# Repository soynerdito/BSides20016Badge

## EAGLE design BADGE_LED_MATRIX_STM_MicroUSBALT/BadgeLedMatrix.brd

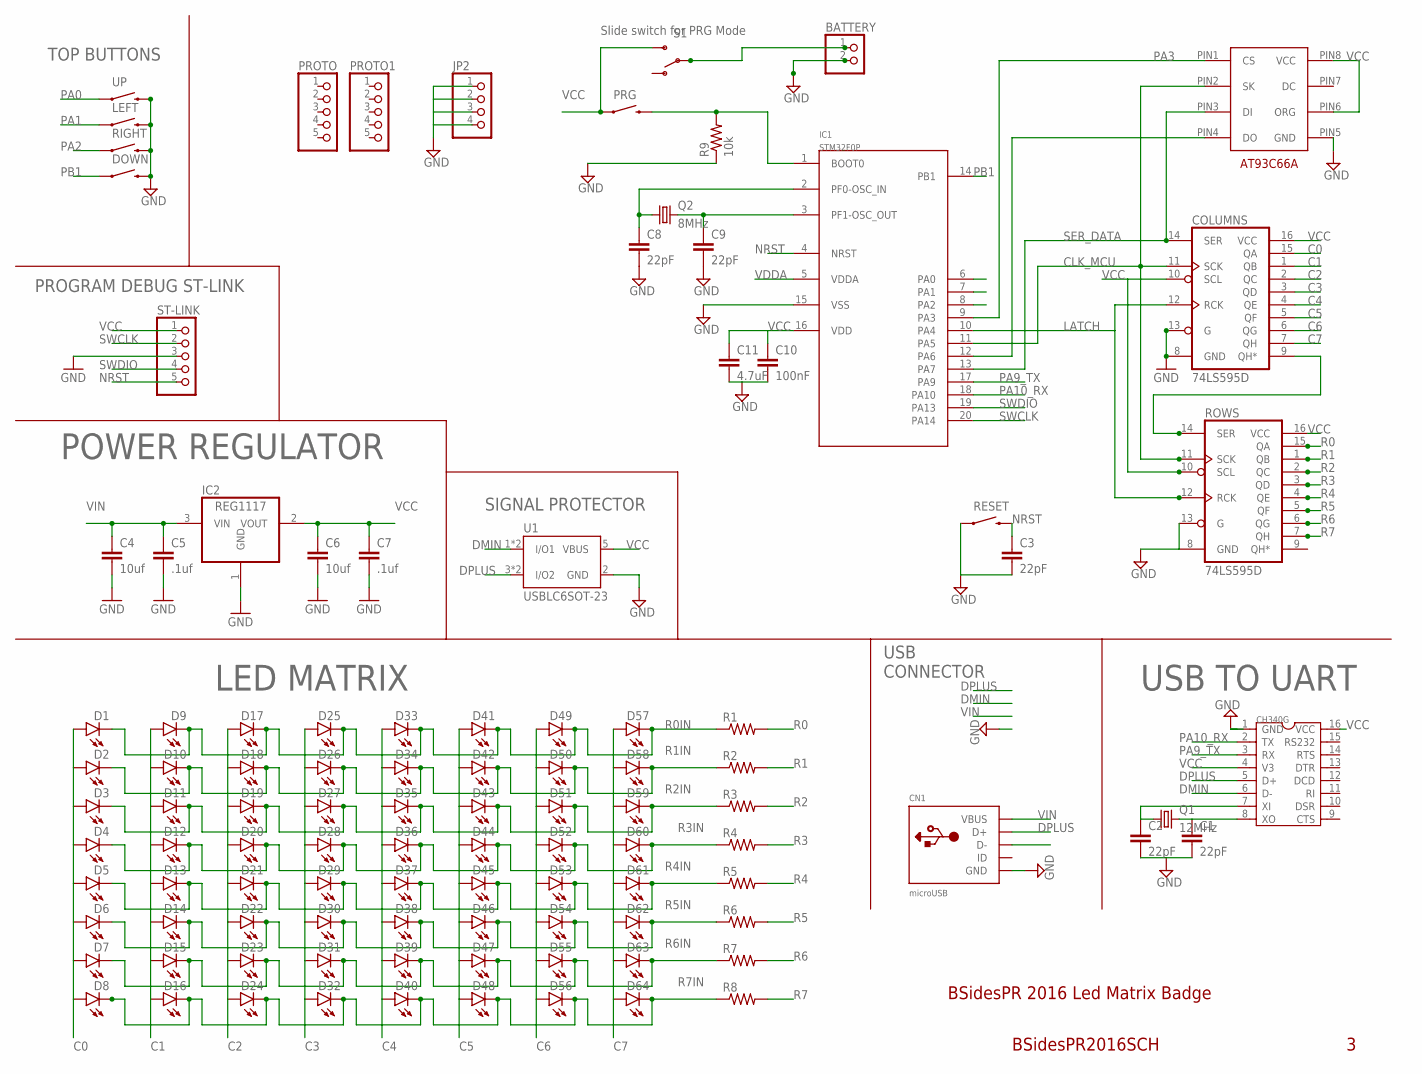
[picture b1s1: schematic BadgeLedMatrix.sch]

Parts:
BATTERY: PINHD-1X2; 1X02
C1, C2, C3, C8, C9: 22pF; 0603-CAP
C4, C6: 10uf; 0603-CAP
C5, C7: .1uf; 0603-CAP
C10: 100nF; 0603-CAP
C11: 4.7uF; 0603-CAP
CH340G: CH340GCH340G; SOP-16
CN1: microUSB; 4UCONN_20329
COLUMNS: 74LS595D; SO16
D1, D2, D3, D4, D5, D6, D7, D8, D9, D10, D11, D12, D13, D14, D15, D16, D17, D18, D19, D20, D21, D22, D23, D24, D25, D26, D27, D28, D29, D30, D31, D32, D33, D34, D35, D36, D37, D38, D39, D40, D41, D42, D43, D44, D45, D46, D47, D48, D49, D50, D51, D52, D53, D54, D55, D56, D57, D58, D59, D60, D61, D62, D63, D64: LED0603; LED-0603
DOWN: SWITCH-MOMENTARY-2SMD-REDUNDANT; TACTILE-SWITCH-SMD
IC1: STM32F0P; TSSOP20
IC2: REG1117; SOT223
JP2: PINHD-1X4; 1X04
LEFT: SWITCH-MOMENTARY-2SMD-REDUNDANT; TACTILE-SWITCH-SMD
PRG: SWITCH-MOMENTARY-2SMD-REDUNDANT; TACTILE-SWITCH-SMD
PROTO, PROTO1: PINHD-1X5; 1X05
Q1: 12MHz; HC49U70
Q2: 8MHz; HC49U70
R1, R2, R3, R4, R5, R6, R7, R8: RESISTOR0603-RES; 0603-RES
R9: 10k; 0603-RES
RESET: SWITCH-MOMENTARY-2SMD-REDUNDANT; TACTILE-SWITCH-SMD
RIGHT: SWITCH-MOMENTARY-2SMD-REDUNDANT; TACTILE-SWITCH-SMD
ROWS: 74LS595D; SO16
S1: SWITCH-SPDT-SMD-A; SWITCH-SPST-SMD-A
ST-LINK: PINHD-1X5; 1X05
U1: USBLC6SOT-23; SOT23-6
U$6: AT93C66A; SOP-8
UP: SWITCH-MOMENTARY-2SMD-REDUNDANT; TACTILE-SWITCH-SMD

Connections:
C0: COLUMNS.15 (QA), D1.A, D2.A, D3.A, D4.A, D5.A, D6.A, D7.A, D8.A
C1: COLUMNS.1 (QB), D9.A, D10.A, D11.A, D12.A, D13.A, D14.A, D15.A, D16.A
C2: COLUMNS.2 (QC), D17.A, D18.A, D19.A, D20.A, D21.A, D22.A, D23.A, D24.A
C3: COLUMNS.3 (QD), D25.A, D26.A, D27.A, D28.A, D29.A, D30.A, D31.A, D32.A
C4: COLUMNS.4 (QE), D33.A, D34.A, D35.A, D36.A, D37.A, D38.A, D39.A, D40.A
C5: COLUMNS.5 (QF), D41.A, D42.A, D43.A, D44.A, D45.A, D46.A, D47.A, D48.A
C6: COLUMNS.6 (QG), D49.A, D50.A, D51.A, D52.A, D53.A, D54.A, D55.A, D56.A
C7: COLUMNS.7 (QH), D57.A, D58.A, D59.A, D60.A, D61.A, D62.A, D63.A, D64.A
CLK_MCU: COLUMNS.11 (SCK), IC1.11 (PA5), ROWS.11 (SCK), U$6.PIN2 (SK)
DMIN: CH340G.6 (D-), CN1.D-, U1.1 (I/O1), U1.4 (I/O1)
DPLUS: CH340G.5 (D+), CN1.D+, U1.3 (I/O2), U1.6 (I/O2)
GND: BATTERY.2, C1.2, C2.2, C3.2, C4.2, C5.2, C6.2, C7.2, C8.2, C9.2, C10.2, C11.2, CH340G.1 (GND), CN1.BASE@1 (GND), CN1.BASE@2 (GND), CN1.GND, CN1.SPRT@1 (GND), CN1.SPRT@2 (GND), CN1.SPRT@3 (GND), CN1.SPRT@4 (GND), COLUMNS.8 (GND), COLUMNS.13 (G), DOWN.3 (2), DOWN.4 (2), IC1.15 (VSS), IC2.1 (GND), JP2.1, JP2.2, JP2.3, JP2.4, LEFT.3 (2), LEFT.4 (2), R9.1, RESET.1, RESET.2 (1), RIGHT.3 (2), RIGHT.4 (2), ROWS.8 (GND), ROWS.13 (G), ST-LINK.3, U1.2 (GND), U$6.PIN5 (GND), UP.3 (2), UP.4 (2)
LATCH: COLUMNS.12 (RCK), IC1.10 (PA4), ROWS.12 (RCK)
unnamed: C9.1, IC1.3 (PF1-OSC_OUT), Q2.2
unnamed: C8.1, IC1.2 (PF0-OSC_IN), Q2.1
unnamed: IC1.1 (BOOT0), PRG.3 (2), PRG.4 (2), R9.2
unnamed: BATTERY.1, S1.2
NRST: C3.1, IC1.4 (NRST), RESET.3 (2), RESET.4 (2), ST-LINK.5
OVERFLOW: COLUMNS.9 (QH*), ROWS.14 (SER)
PA0: IC1.6 (PA0), UP.1, UP.2 (1)
PA1: IC1.7 (PA1), LEFT.1, LEFT.2 (1)
PA2: IC1.8 (PA2), RIGHT.1, RIGHT.2 (1)
PA3: IC1.9 (PA3), U$6.PIN1 (CS)
PA6: IC1.12 (PA6), U$6.PIN4 (DO)
PA9_TX: CH340G.3 (RX), IC1.17 (PA9)
PA10_RX: CH340G.2 (TX), IC1.18 (PA10)
PB1: DOWN.1, DOWN.2 (1), IC1.14 (PB1)
R0: R1.2, ROWS.15 (QA)
R0IN: D1.C, D9.C, D17.C, D25.C, D33.C, D41.C, D49.C, D57.C, R1.1
R1: R2.2, ROWS.1 (QB)
R1IN: D2.C, D10.C, D18.C, D26.C, D34.C, D42.C, D50.C, D58.C, R2.1
R2: R3.2, ROWS.2 (QC)
R2IN: D3.C, D11.C, D19.C, D27.C, D35.C, D43.C, D51.C, D59.C, R3.1
R3: R4.2, ROWS.3 (QD)
R3IN: D4.C, D12.C, D20.C, D28.C, D36.C, D44.C, D52.C, D60.C, R4.1
R4: R5.2, ROWS.4 (QE)
R4IN: D5.C, D13.C, D21.C, D29.C, D37.C, D45.C, D53.C, D61.C, R5.1
R5: R6.2, ROWS.5 (QF)
R5IN: D6.C, D14.C, D22.C, D30.C, D38.C, D46.C, D54.C, D62.C, R6.1
R6: R7.2, ROWS.6 (QG)
R6IN: D7.C, D15.C, D23.C, D31.C, D39.C, D47.C, D55.C, D63.C, R7.1
R7: R8.2, ROWS.7 (QH)
R7IN: D8.C, D16.C, D24.C, D32.C, D40.C, D48.C, D56.C, D64.C, R8.1
SER_DATA: COLUMNS.14 (SER), IC1.13 (PA7), U$6.PIN3 (DI)
SWCLK: IC1.20 (PA14), ST-LINK.2
SWDIO: IC1.19 (PA13), ST-LINK.4
VCC: C6.1, C7.1, C10.1, C11.1, CH340G.4 (V3), CH340G.16 (VCC), COLUMNS.10 (SCL), COLUMNS.16 (VCC), IC1.16 (VDD), IC2.2 (VOUT), PRG.1, PRG.2 (1), ROWS.10 (SCL), ROWS.16 (VCC), S1.3 (S), ST-LINK.1, U1.5 (VBUS), U$6.PIN6 (ORG), U$6.PIN8 (VCC)
VDDA: IC1.5 (VDDA)
VIN: C4.1, C5.1, CN1.VBUS, IC2.3 (VIN)
XI: C2.1, CH340G.7 (XI), Q1.1
XO: C1.1, CH340G.8 (XO), Q1.2

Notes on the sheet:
POWER REGULATOR
LED MATRIX
USB TO UART
USB CONNECTOR
SIGNAL PROTECTOR
BSidesPR 2016 Led Matrix Badge
BSidesPR2016SCH
PROGRAM DEBUG ST-LINK
TOP BUTTONS
Slide switch for PRG Mode

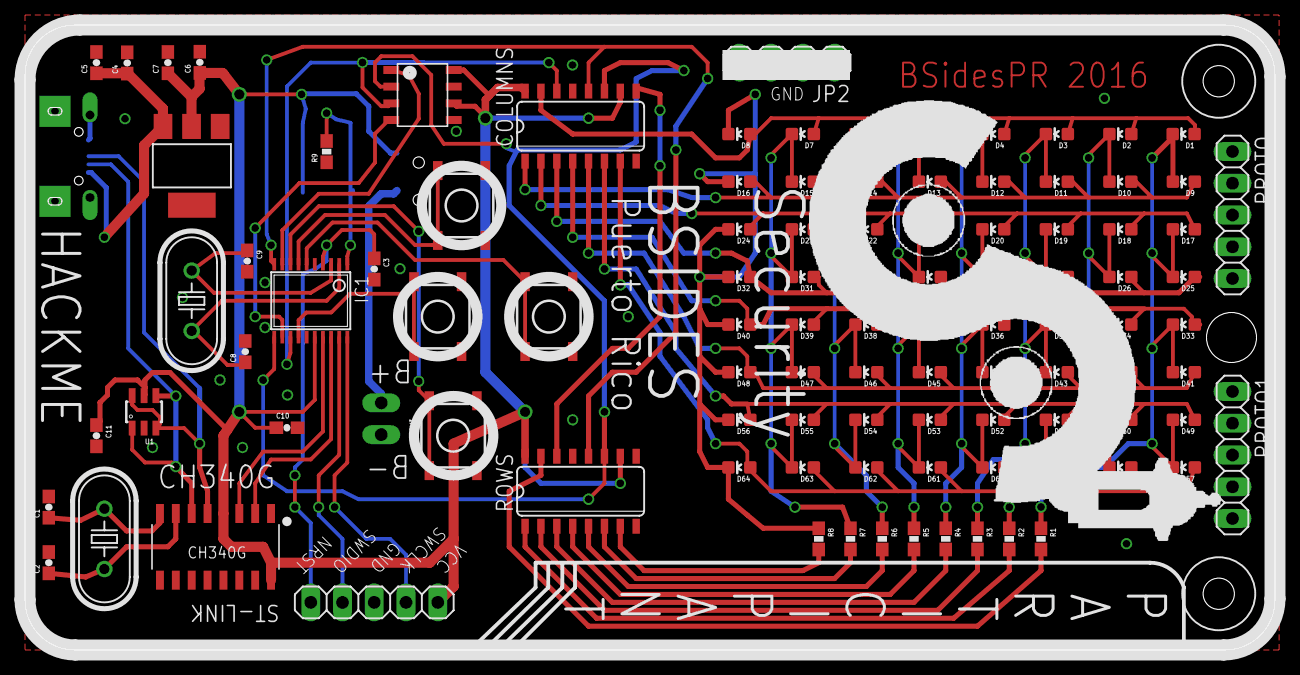
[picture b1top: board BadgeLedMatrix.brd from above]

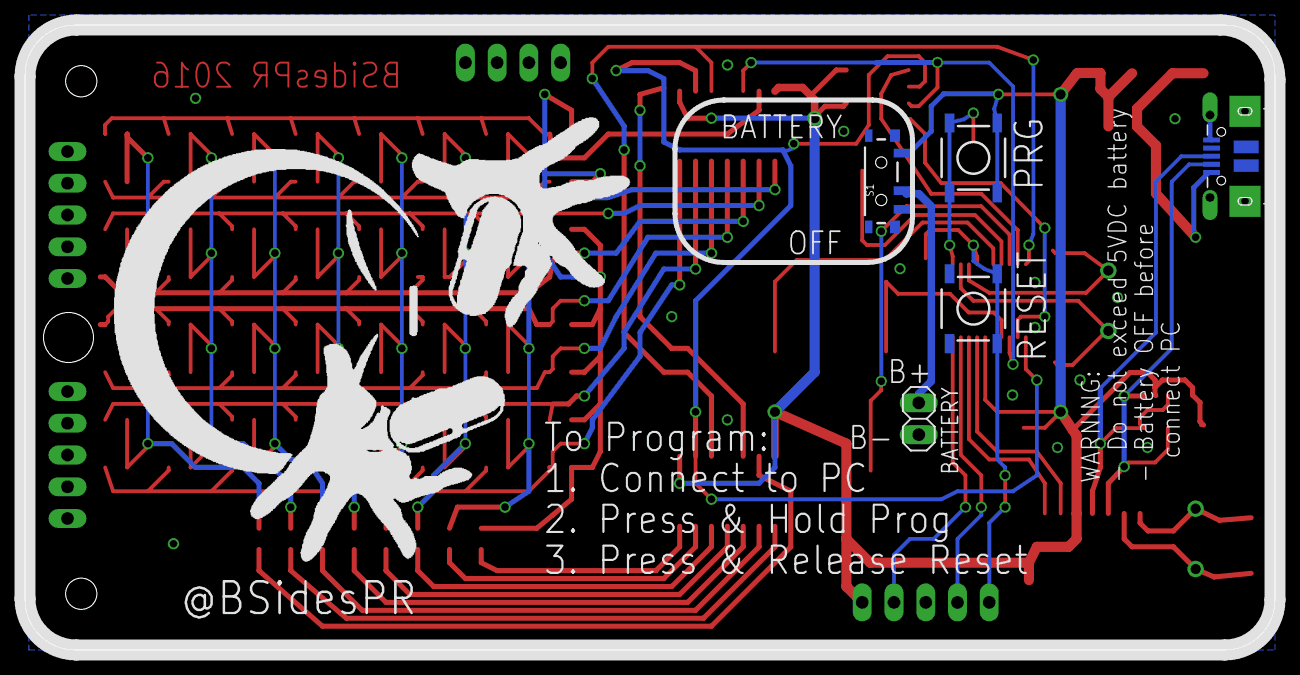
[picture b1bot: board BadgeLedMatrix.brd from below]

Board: 2 copper layers, 100.0 x 50.0 mm, 110 parts (5 on the bottom side), 50 nets.

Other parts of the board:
U$1: OBSIDISLOGO_BOTTOM
U$2: BSIDES_LOGO_NTB_PIC_ONLY
U$3, U$5: DRIL-2,5

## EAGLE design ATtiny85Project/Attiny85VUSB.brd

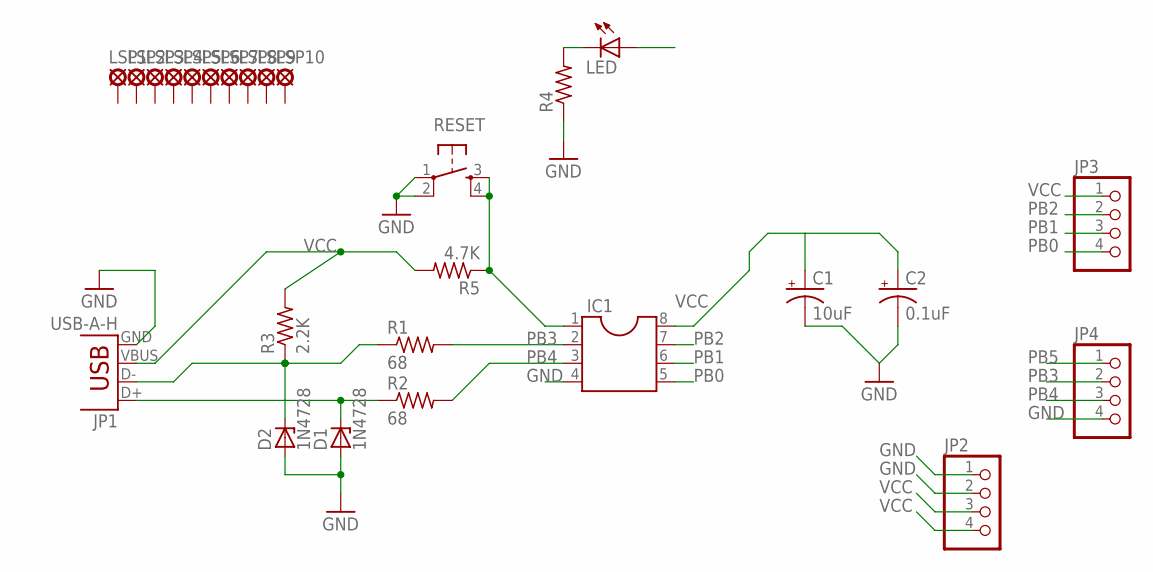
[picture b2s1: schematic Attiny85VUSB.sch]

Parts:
C1: 10uF; CPOL-RADIAL-100UF-25V
C2: 0.1uF; CPOL-RADIAL-100UF-25V
D1, D2: 1N4728; DO41Z10
IC1: ATTINY85TESTS; SOCKET-08
JP1: USB-A-H
JP2, JP3, JP4: PINHD-1X4; 1X04
LED: LED5MM
LSP1, LSP2, LSP3, LSP4, LSP5, LSP6, LSP7, LSP8, LSP9, LSP10: MCS08
R1, R2: 68; 0207/9
R3: 2.2K; 0207/9
R4: R-US_0207/9; 0207/9
R5: 4.7K; 0207/9
RESET: TAC_SWITCHPTH; TACTILE-PTH

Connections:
DMIN: D2.C, JP1.D-, R1.1, R3.1
DPLUS: D1.C, JP1.D+, R2.1
GND: C1.2 (-), C2.2 (-), D1.A, D2.A, IC1.4 (GND), JP1.GND, JP2.1, JP2.2, JP4.4, R4.1, RESET.1, RESET.2
unnamed: LED.K (C), R4.2
PB0: IC1.5 (PB0MOSI), JP3.4
PB1: IC1.6 (PB1_MISO), JP3.3, LED.A
PB2: IC1.7 (PB2SCK), JP3.2
PB3: IC1.2 (PB3_CLKI), JP4.2, R1.2
PB4: IC1.3 (PB4_CLKO), JP4.3, R2.2
PB5: JP4.1
RESET: IC1.1 (PB5_~RESET), R5.1, RESET.3, RESET.4
VCC: C1.1 (+), C2.1 (+), IC1.8 (VCC), JP1.VBUS, JP2.3, JP2.4, JP3.1, R3.2, R5.2

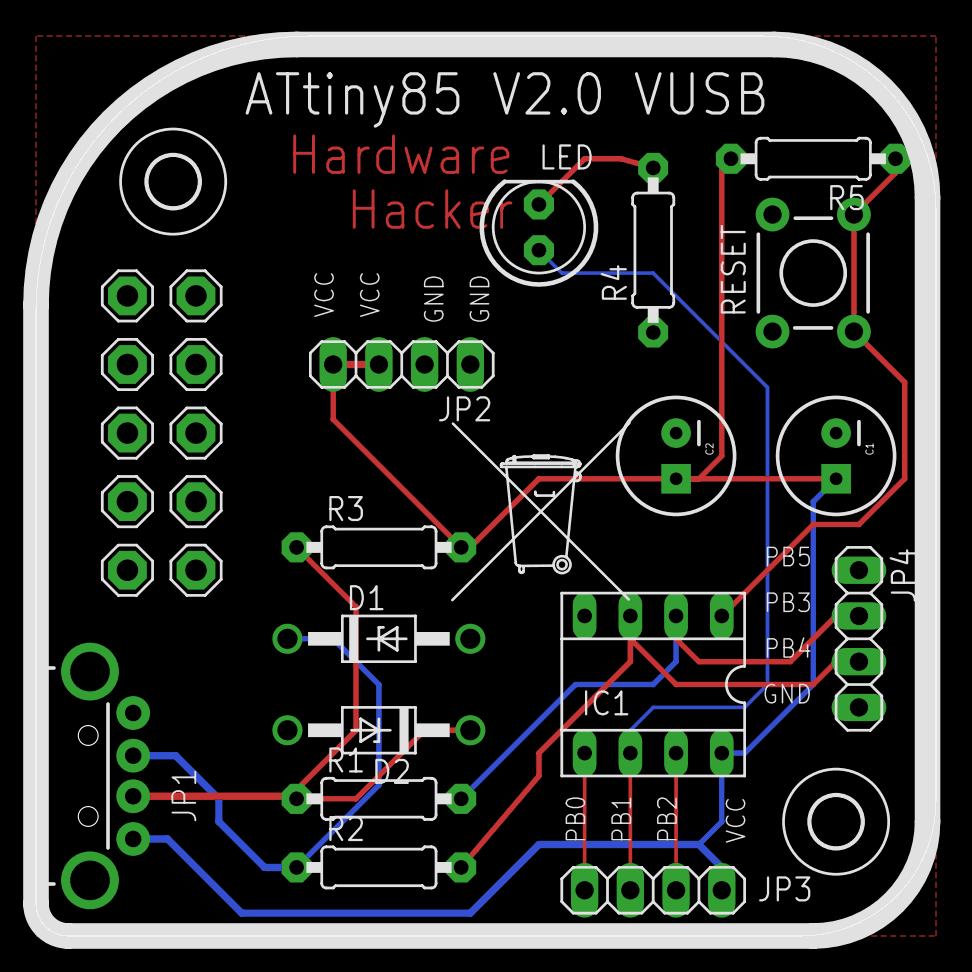
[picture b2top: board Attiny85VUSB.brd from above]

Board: 2 copper layers, 50.0 x 50.0 mm, 31 parts (1 on the bottom side), 11 nets.

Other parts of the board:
U$1, U$2: TONNE_10.00
U$3, U$4: 2,8
U$5: LOGO

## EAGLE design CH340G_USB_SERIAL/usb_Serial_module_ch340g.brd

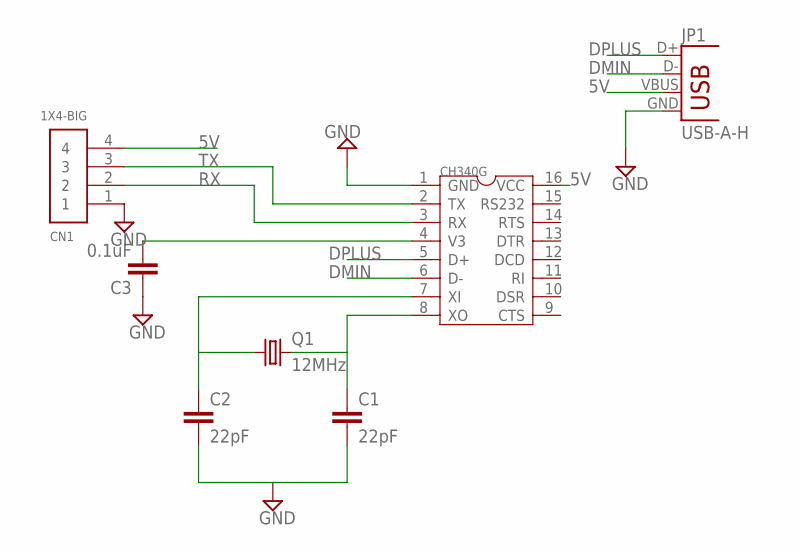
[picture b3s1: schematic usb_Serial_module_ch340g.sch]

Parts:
C1, C2: 22pF; 0603-CAP
C3: 0.1uF; 0603-CAP
CH340G: CH340GCH340G; SOP-16
CN1: 1X4-BIG; 1X04-BIG
JP1: USB-A-H
Q1: 12MHz; HC49U70

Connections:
5V: CH340G.16 (VCC), CN1.4, JP1.VBUS
DMIN: CH340G.6 (D-), JP1.D-
DPLUS: CH340G.5 (D+), JP1.D+
GND: C1.2, C2.2, C3.1, CH340G.1 (GND), CN1.1, JP1.GND
unnamed: C3.2, CH340G.4 (V3)
RX: CH340G.3 (RX), CN1.2
TX: CH340G.2 (TX), CN1.3
XI: C2.1, CH340G.7 (XI), Q1.1
XO: C1.1, CH340G.8 (XO), Q1.2

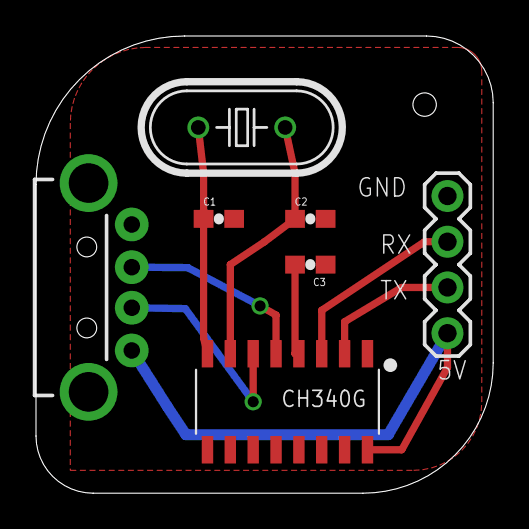
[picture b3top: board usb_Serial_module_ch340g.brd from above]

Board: 2 copper layers, 25.4 x 25.4 mm, 7 parts (0 on the bottom side), 9 nets.

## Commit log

2015-12-09 Updating circuit diagram
2015-12-10 Fix for connection of VCC from shift registers
2015-12-10 Small touch ups
2015-12-10 Notes to verify first prototype when getting back from production, possible VCC and Ground not-connected
2015-12-18 Board diode orientation fix, board corners, allignment of top corner holes
2015-12-18 Fixing board white border, top and bottom
2016-02-26 Added EPROM and wired up buttons
2016-02-27 Prototype 2, Ordered. Added EPROM, Slide Switch for PROG
2016-03-01 Same board with a different microusb connector just to test if easier to solder
2016-03-01 Updating Circuit images
2016-03-22 Small fixes to attiny85 to use other pins
2016-03-22 Rewire ATtiny85 board to make it compatible with triket
2016-03-23 Testing for V2 of the board, sent to fab
2016-03-28 Prototype V4 with PL2303HX USB to UART chip. Testing to check if is better supported and maybe cheaper.
2016-04-26 don't know what changed
2016-04-26 Speaker badge
2016-04-26 Ordered staff & speaker
2016-06-28 Updating for participant

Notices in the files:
parts and their libraries:
SparkFun-Capacitors: Licensing: Creative Commons ShareAlike 4.0 International - https://creativecommons.org/licenses/by-sa/4.0
microbuilder: This work is placed in the public domain, and may be freely used for commercial and non-commercial work with the following conditions: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
